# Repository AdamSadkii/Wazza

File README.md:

# Wazza - Magic in The Air

Wazza is a fully open-source, gesture-controlled AI wand that translates physical hand motions into real-time digital commands. By tracking movement via an internal MPU-6050 6-axis IMU, the onboard ESP32-S3 Mini microcontroller processes gesture vectors, coordinates peripheral systems, and streams telemetry data to an onboard OLED screen alongside audio feedback through an integrated I2S speaker interface.

## Key Features

- 1 x ESP32-S3-MINI-1 Microcontroller (Main Brain)
- 1 x MPU-6050 6-Axis Motion Sensor (IMU)
- 1 x MAX98357A I2S Audio Amplifier & 2W Speaker
- 1 x SPH0645 I2S MEMS Microphone
- 1 x 18650 LiPo Battery Cell
- 1 x TP4056 USB-C Battery Charger Module
- 1 x Tactile Push Button (Momentary switch)
- 1 x WS2812B RGB LED Strip (15-20 LEDs)
- 10 x Resistors (For the required I2C data/clock pull-ups)
- 3 x Electrolytic Capacitors

## How to get the code (not on Vercel)

This is not hosted on Vercel. You grab it from GitHub and run it on your PC.

1. Go to https://github.com/AdamSadkii/Wazza
2. Hit the green Code button
3. Click Download ZIP (or clone it if you use git)
4. Unzip it
5. Open the folder in VS Code / Cursor (or open `Wazza.code-workspace`)

Folders you care about:
- `frontend/` = dashboard
- `backend/` = python server + AI
- `firmware/` = ESP32 code

## Run it on your PC

1. Open a terminal in `backend`
2. Make a venv: `python -m venv .venv`
3. Activate it: `.\.venv\Scripts\Activate.ps1`
4. Install deps: `pip install -r requirements.txt`
5. Run it: `python server.py`
6. Open http://localhost:8000 in your browser

Optional AI:
- set `OPENAI_API_KEY` or run Ollama locally

## Flash the wand

1. Copy `firmware/src/secrets.example.h` to `firmware/src/secrets.h`
2. Put your wifi name/password in there
3. Put your PC IP in `BACKEND_HOST` (port 8765)
4. Open `firmware/` in PlatformIO
5. Build + upload to the ESP32-S3
6. Keep `python server.py` running so the wand can connect

## Schematic

The schematic composes a well organized layout of each system in the device, ranging from power management to the microcontroller itself. This lays the ideal blueprint for the PCB.

The power system (powered by a USB-C component, is the base component of the whole project. A user plugs in a wire in order to actually connect to the code itself, and allow the Ai to run within itself. That way the user can just prompt using the commanded gestures it follows.

## PCB

## Future Enhancements

Potential improvements include on-device machine learning for gesture recognition to reduce API latency, integration with additional sensors like IMUs or proximity detectors, wireless charging capability, and support for custom gesture training. The modular design allows for easy hardware upgrades without redesigning the entire system.

## Files and Documentation

The project includes complete KiCAD schematic files organized by functional module, PCB layout files for fabrication, Arduino firmware source code with gesture templates, and assembly instructions with wiring diagrams. All code is open source and available for modification and redistribution.

## CADDED Module

## Thank you.
A big thanks to Nesh, Keam, and Yahya for being part of the process the whole way. Without them I don't think I would've been able to make it as far.
deduct 2 hrs

## License: MIT

Copyright 2026

Permission is hereby granted, free of charge, to any person obtaining a copy of this software and associated documentation files (the "Software"), to deal in the Software without restriction, including without limitation the rights to use, copy, modify, merge, publish, distribute, sublicense, and/or sell copies of the Software, and to permit persons to whom the Software is furnished to do so, subject to the following conditions:

The above copyright notice and this permission notice shall be included in all copies or substantial portions of the Software.

THE SOFTWARE IS PROVIDED "AS IS", WITHOUT WARRANTY OF ANY KIND, EXPRESS OR IMPLIED, INCLUDING BUT NOT LIMITED TO THE WARRANTIES OF MERCHANTABILITY, FITNESS FOR A PARTICULAR PURPOSE AND NONINFRINGEMENT. IN NO EVENT SHALL THE AUTHORS OR COPYRIGHT HOLDERS BE LIABLE FOR ANY CLAIM, DAMAGES OR OTHER LIABILITY, WHETHER IN AN ACTION OF CONTRACT, TORT OR OTHERWISE, ARISING FROM, OUT OF OR IN CONNECTION WITH THE SOFTWARE OR THE USE OR OTHER DEALINGS IN THE SOFTWARE.

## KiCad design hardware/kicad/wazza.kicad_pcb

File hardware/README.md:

# Wazza hardware

| Path | What |
|------|------|
| `kicad/` | KiCad 10 project (schematics + routed PCB) |
| `cad/Wand3.step` | Enclosure CAD (Onshape / Wand3 export) |
| `gerbers/` | Gerber + Excellon drill (+ `wazza_gerbers.zip`) |
| `wiring/` | Schematic PDF + PCB preview / routed renders |
| `WIRING.md` | Net / pin map |
| `ASSEMBLY.md` | Build and assembly steps |

Open `kicad/wazza.kicad_pro` in **KiCad 10**.

## Quick fab

Upload `gerbers/wazza_gerbers.zip` to JLCPCB / PCBWay (or similar).  
Board outline: **155 × 26 mm**, 2-layer.

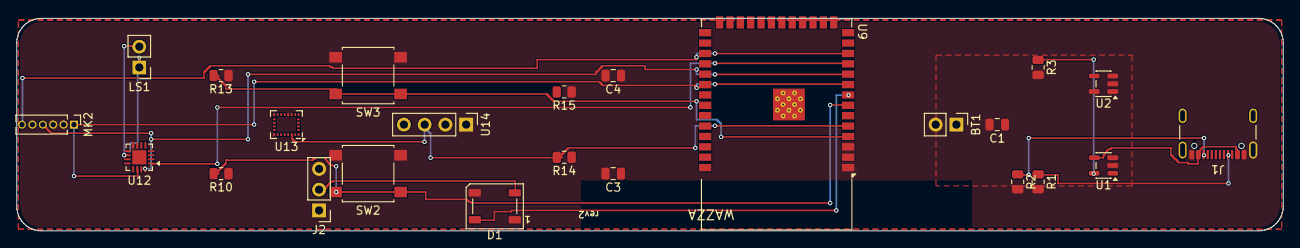
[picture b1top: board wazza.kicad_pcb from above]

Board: 2 copper layers, 155.0 x 26.0 mm, 24 parts (0 on the bottom side), 19 nets.

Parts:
BT1: PinHeader_1x02_P2.54mm_Vertical
C1, C3, C4: C_0805_2012Metric
D1: LED_WS2812B_PLCC4_5.0x5.0mm_P3.2mm
J1: USB_C_Receptacle_GCT_USB4105-xx-A_16P_TopMnt_Hori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; USB_C_Receptacle_GCT_USB4105-xx-A_16P_TopMnt_Horizontal
J2: PinHeader_1x03_P2.54mm_Vertical
LS1: PinHeader_1x02_P2.54mm_Vertical
MK2: PinHeader_1x06_P1.27mm_Vertical
R1, R2, R3, R10, R13, R14, R15: R_0805_2012Metric
SW2, SW3: SW_SPST_B3S-1000
U1, U2: SOT-23-5
U9: ESP32-S3-WROOM-1
U12: QFN-16-1EP_3x3mm_P0.5mm_EP1.7x1.7mm
U13: LGA-24L_3x3.5mm_P0.43mm
U14: PinHeader_1x04_P2.54mm_Vertical

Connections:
+3V3: C1.1, C3.1, C4.1, D1.1, J2.1, MK2.5, R10.1, R13.1, R14.1, R15.1, U2.5, U9.2, U9.3, U12.7, U13.8, U13.13, U14.2
/05_LEDs_Buttons/LED_DOUT: D1.2, J2.2
AMP_DIN: U9.11, U12.1
BTN_ACTION: R10.2, SW2.1, U9.7
BTN_BOOT: R13.2, SW3.1, U9.4
GND: BT1.2, C1.2, C3.2, C4.2, D1.3, J1.A1, J1.A12, J1.B1, J1.B12, J1.SH, J2.3, MK2.2, MK2.3, R1.2, R2.2, R3.2, SW2.2, SW3.2, U1.2, U2.2, U9.1, U12.8, U12.17, U13.9, U13.18, U14.1
I2S_BCLK: MK2.4, U9.10, U12.16
I2S_LRCLK: MK2.1, U9.9, U12.14
LED_DIN: D1.4, U9.8
MIC_DOUT: MK2.6, U9.12
unnamed: BT1.1, U1.3, U2.1, U2.3
unnamed: J1.A5, R1.1
unnamed: J1.B5, R2.1
unnamed: R3.1, U1.5
unnamed: J1.A4, J1.A9, J1.B4, J1.B9, U1.4
unnamed: LS1.2, U12.10
unnamed: LS1.1, U12.9
SCL: R14.2, U9.5, U13.23, U14.3
SDA: R15.2, U9.6, U13.24, U14.4

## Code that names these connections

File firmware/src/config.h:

#pragma once

// I2C SDA and SCL. (MPU-6050 & OLED)
#define PIN_I2C_SDA 5
#define PIN_I2C_SCL 4

// WS2812 LEDs.
#define PIN_WS2812_DIN 18
#define NUM_LEDS 16
#define LED_BRIGHTNESS 80

// Buttons.
#define PIN_BTN_BOOT 0
#define PIN_BTN_ACTION 8
#define BTN_ACTIVE_HIGH 0

// I2S pins. (Audio)
#define PIN_I2S_BCLK 26
#define PIN_I2S_LRCLK 21
#define PIN_I2S_AMP_DIN 33
#define PIN_I2S_MIC_DOUT 34

// OLED display.
#define OLED_WIDTH 128
#define OLED_HEIGHT 32
#define OLED_I2C_ADDRESS 0x3C

// Gestures (Motion detection thresholds and timing)
#define PIN_GESTURE_SAMPLE_HZ 100
#define FLICK_THRESHOLD 12.0f
#define FLICK_HARD_THRESHOLD 18.0f
#define SWIPE_THRESHOLD 5.0f
#define SHAKE_THRESHOLD 15.0f
#define CIRCLE_GYRO_MIN 4.0f
#define GESTURE_COOLDOWN_MS 500
#define HOLD_MS 900

// Telemetry / Net
#define TELEMETRY_INTERVAL_MS 100
#define WS_RECONNECT_MS 2000
#define WIFI_CONNECT_TIMEOUT_MS 20000

// Features
#define ENABLE_AUDIO 1
#define ENABLE_OLED 1
#define ENABLE_LEDS 1
#define ENABLE_IMU 1

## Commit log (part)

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2026-06-29 Add journal entry for schematic completion
    Documented the completion of the schematic with design decisions, architecture, and next steps.
2026-06-29 Add image to README for project visualizationima
    Added an image to the README for better visualization.
2026-06-29 Add schematic image to README
2026-06-29 Revise AI interaction description in README
    Updated project description to refer to AI Agents instead of Claude AI.
2026-06-29 Update schematic completion entry with time spent
    Added time spent to the schematic completion entry.
2026-06-29 Add first hour entry with image to Journalphotos.md
2026-06-29 Document Day 6 progress on PCB organization
    Added Day 6 reflection on PCB organization and progress.
2026-06-29 Document progress on PCB organization
    Added reflections on the PCB organization process.
2026-06-29 Update README with new schematic and future enhancements
    Added a new schematic image and outlined potential future enhancements for the project.
2026-06-29 Fix major PCB layout errors and improve schematic
    Corrected wiring paths for resistors R4 and R5 on the PCB layout, fixing a major error that affected the communication loop. Made additional adjustments to address widespread design flaws in the sche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
2026-06-30 Update journal with Day 2 PCB progress
    Document progress on PCB creation, including challenges with wiring and plans for future improvements.
2026-06-30 Revise Journal Day to 6/29/26 and update content
    Updated journal entry date and details about PCB progress.
2026-06-30 Add new images to Journalphotos.md
    Added two new images to the Journalphotos section.
2026-06-30 Document schematic rewire and ESP32 module update
    Updated the journal with progress on schematic rewiring and ESP32 module clarification.
2026-06-30 Add images for Hours 3-4 in Journalphotos.md
    Added images for Hours 3-4 on 6/30/2026.
2026-06-30 Document schematic rewire progress in journal
    Updated the journal with details on schematic rewiring and ESP32-S3 Mini usage.
2026-06-30 Revise journal entries for PCB layout progress
    Updated journal entries to reflect progress on PCB layout and troubleshooting steps taken with the ESP32 module. Added sections on design decisions, architecture, and next steps for the project.
2026-06-30 Add new section and images to Journalphotos.md
    Added new images and section for hours 4-5 on 6/30/2026.
